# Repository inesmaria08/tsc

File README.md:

# InkTime Smartwatch v5 - Documentație Hardware (DVT)

Acest repository conține pachetul complet de proiectare hardware (schematică, layout PCB, fișiere de fabricație) pentru **InkTime**, un smartwatch ultra-low-power. Proiectul este axat pe eficientizarea consumului energetic și integrarea unui afișaj bi-stabil, eliminând limitările de autonomie specifice dispozitivelor portabile convenționale.

---

## 1. Subsisteme Hardware Integrate

Arhitectura sistemului a fost segmentată în blocuri funcționale clare, utilizând componente specializate pentru a minimiza consumul de energie în modul stand-by (parasitic draw).

### 1.1. Microcontroller și RF
Implementarea are la bază SoC-ul **Nordic Semiconductor nRF52840**, selectat pentru eficiența superioară în gestionarea stivei Bluetooth 5.0 (BLE). Secțiunea RF integrează o antenă ceramică SMD de 2.45GHz (Johanson 2450AT18). Pentru a menține integritatea semnalului radio și a asigura o propagare optimă, zona de sub antenă a fost tratată ca o zonă strictă de "Keep-out", fiind complet izolată de planurile de cupru pe toate straturile PCB-ului.

### 1.2. Power Management Unit (PMIC)
Pentru a garanta o funcționare stabilă a display-ului e-Paper, sensibil la fluctuațiile de tensiune specifice descărcării acumulatorului Li-Po, arhitectura de alimentare exclude regulatoarele LDO clasice în favoarea unor soluții cu randament ridicat:
* **RT6160A:** Regulator Buck-Boost de înaltă eficiență, capabil să mențină o ieșire stabilă de 3.3V pe întreg parcursul descărcării bateriei (4.2V - 3.0V).
* **BQ25180:** Circuit integrat de încărcare liniară, conectat direct la portul USB-C (16-pin) și protejat împotriva descărcărilor electrostatice (ESD) de cipul USBLC6-2SC6Y.
* **MAX17048:** Fuel Gauge care implementează algoritmul ModelGauge pentru monitorizarea precisă a stării de încărcare a bateriei (State of Charge), eliminând necesitatea unui rezistor de shunt și comunicând via I2C.

### 1.3. Interfață Utilizator și Senzori
* **Display e-Paper:** Conectat prin intermediul magistralei SPI (conector Molex FPC cu 24 de pini). Datorită tehnologiei bi-stabile, consumul de curent pentru reținerea imaginii este nul.
* **IMU (Inertial Measurement Unit):** Accelerometrul triaxial ultra-low-power Bosch BMA423 este utilizat pentru detectarea mișcării și activarea sistemului (tilt-to-wake), comunicând prin I2C și semnale de întrerupere hardware.
* **Feedback Haptic:** Driver-ul DRV2605 (Texas Instruments) controlează motorul de vibrație ERM, gestionând efecte haptice pre-procesate fără a încărca suplimentar procesorul principal.
* **Input Hardware:** Trei butoane tactile SMD conectate direct la porturile GPIO (cu rezistențe pull-up interne) pentru navigarea în meniul dispozitivului.

---

## 2. Considerente de Producție (PCBA) și Reguli DFM

Designul a fost optimizat riguros pentru a îndeplini cerințele fabricării la scară (Design for Manufacturing) și pentru a asigura o integrare mecanică perfectă în carcasa smartwatch-ului:

1. **Optimizare PCBA:** Toate componentele SMD sunt plasate exclusiv pe stratul superior (TOP Layer). Această abordare reduce masiv complexitatea, timpul și costurile procesului automatizat Pick & Place. Placa de bază a fost proiectată pentru o grosime a substratului de 1.0mm, vitală pentru menținerea unui profil subțire (low-profile) al ansamblului final.
2. **Reguli de Rutare și Putere:** Traseele de alimentare (VCC, VBUS, 3V3) au fost rutate cu o lățime sigură de minimum 0.3mm pentru a suporta vârfurile de consum (în special în timpul refresh-ului e-Paper și activării motorului haptic). Magistralele de semnal de mare viteză utilizează o lățime de 0.15mm.
3. **Integritate RF și Planuri de Masă:** S-au implementat planuri de masă continue (GND) atât pe stratul TOP, cât și pe BOTTOM. S-a utilizat tehnica de "via stitching" manual, cu o densitate crescută în proximitatea circuitului radio și a convertorului DC/DC, pentru a oferi o cale de retur de impedanță minimă și a reduce emisiile EMI.

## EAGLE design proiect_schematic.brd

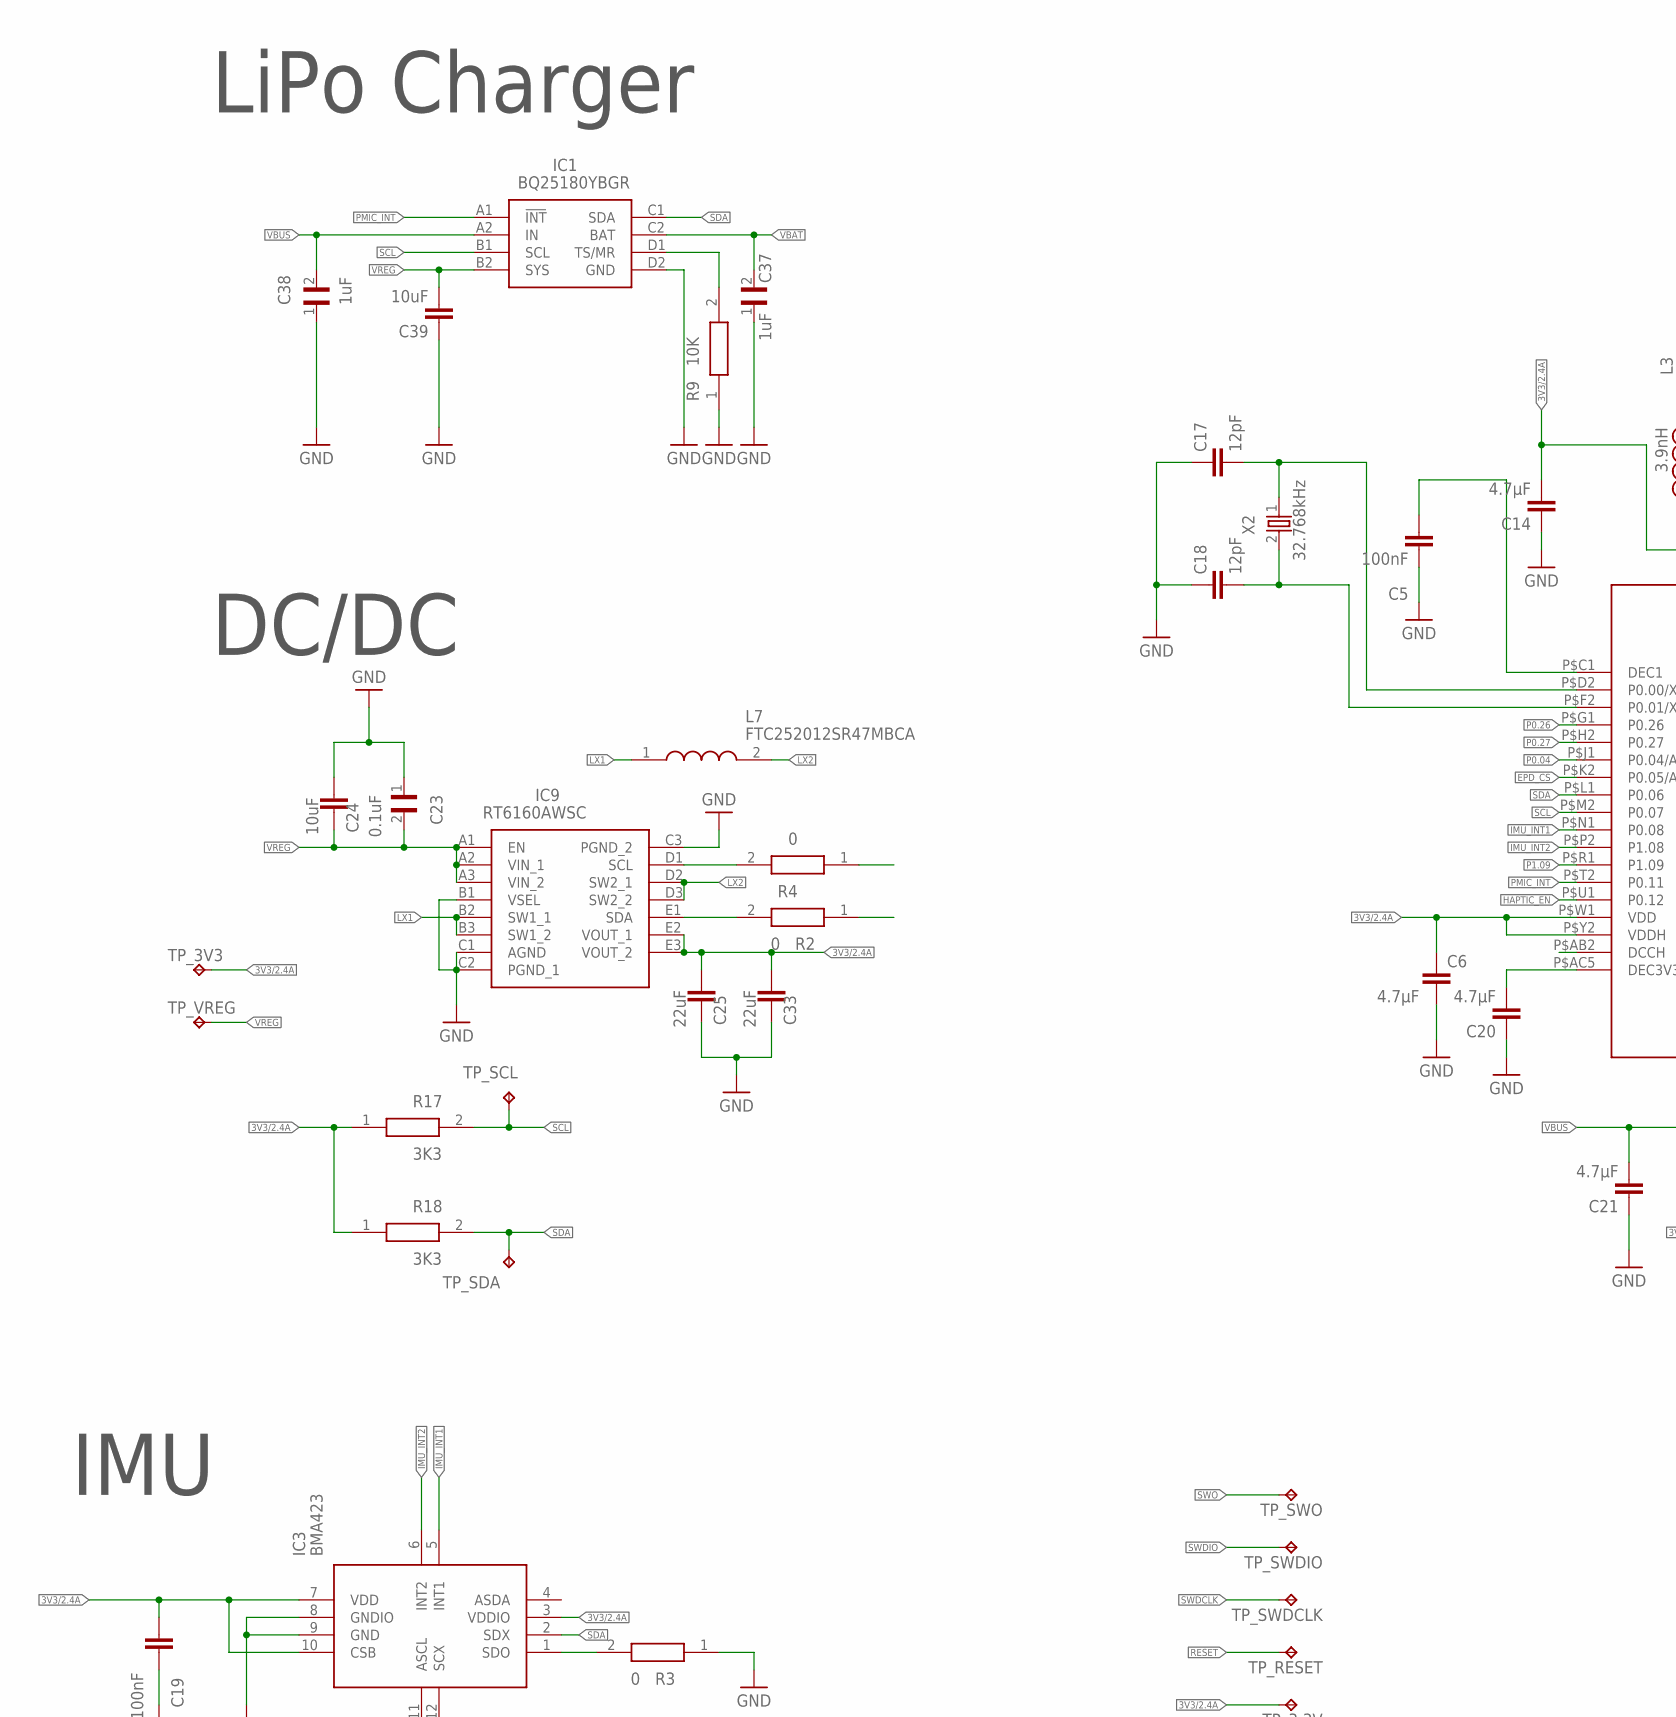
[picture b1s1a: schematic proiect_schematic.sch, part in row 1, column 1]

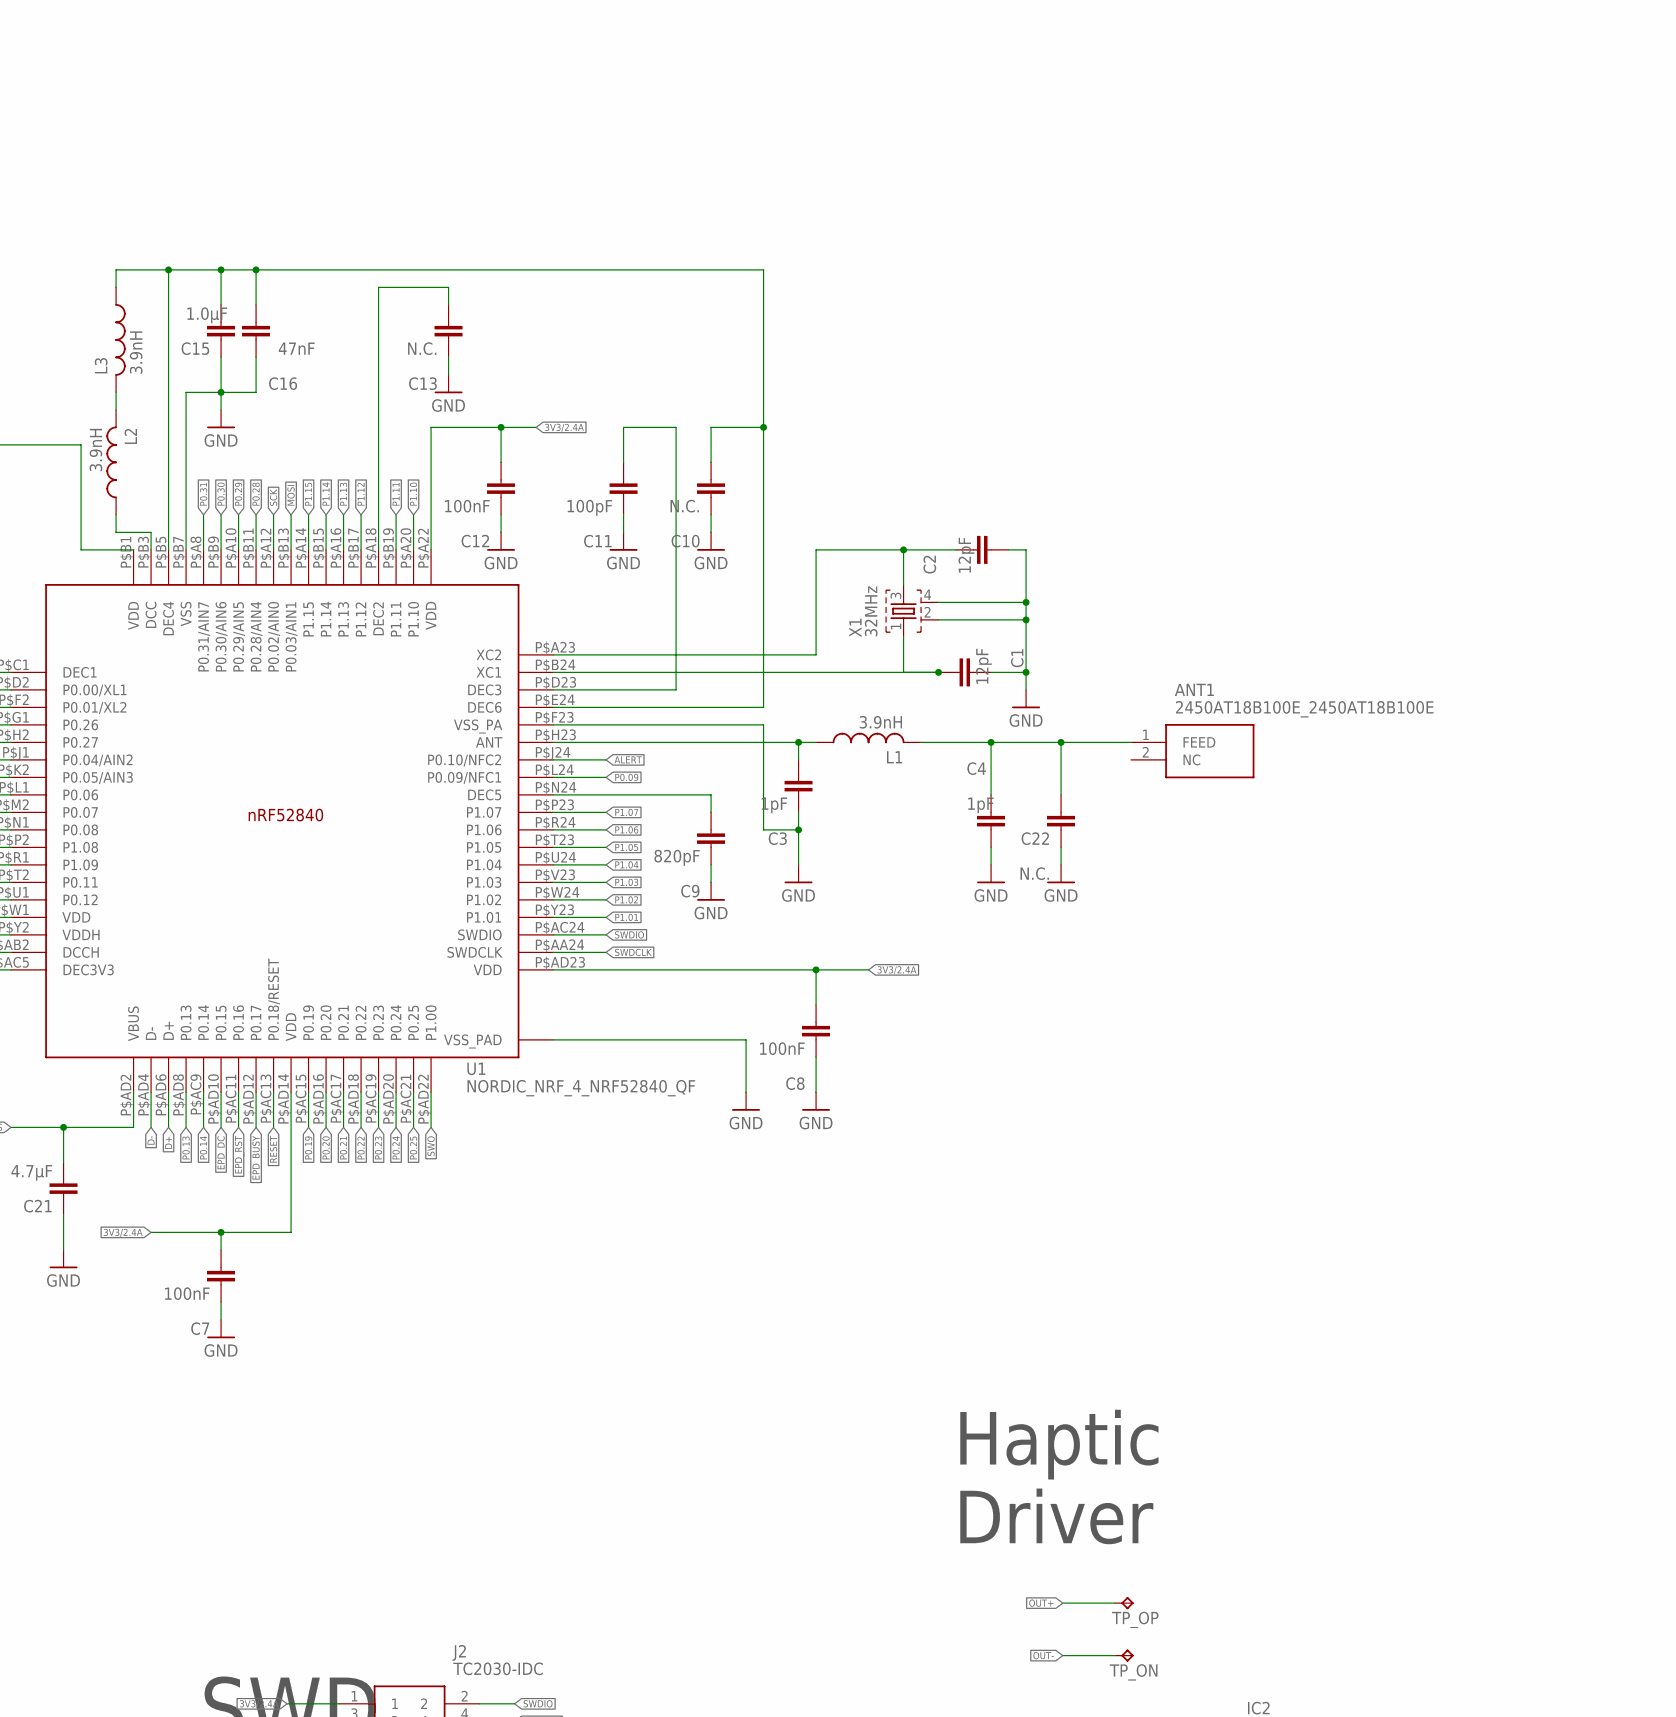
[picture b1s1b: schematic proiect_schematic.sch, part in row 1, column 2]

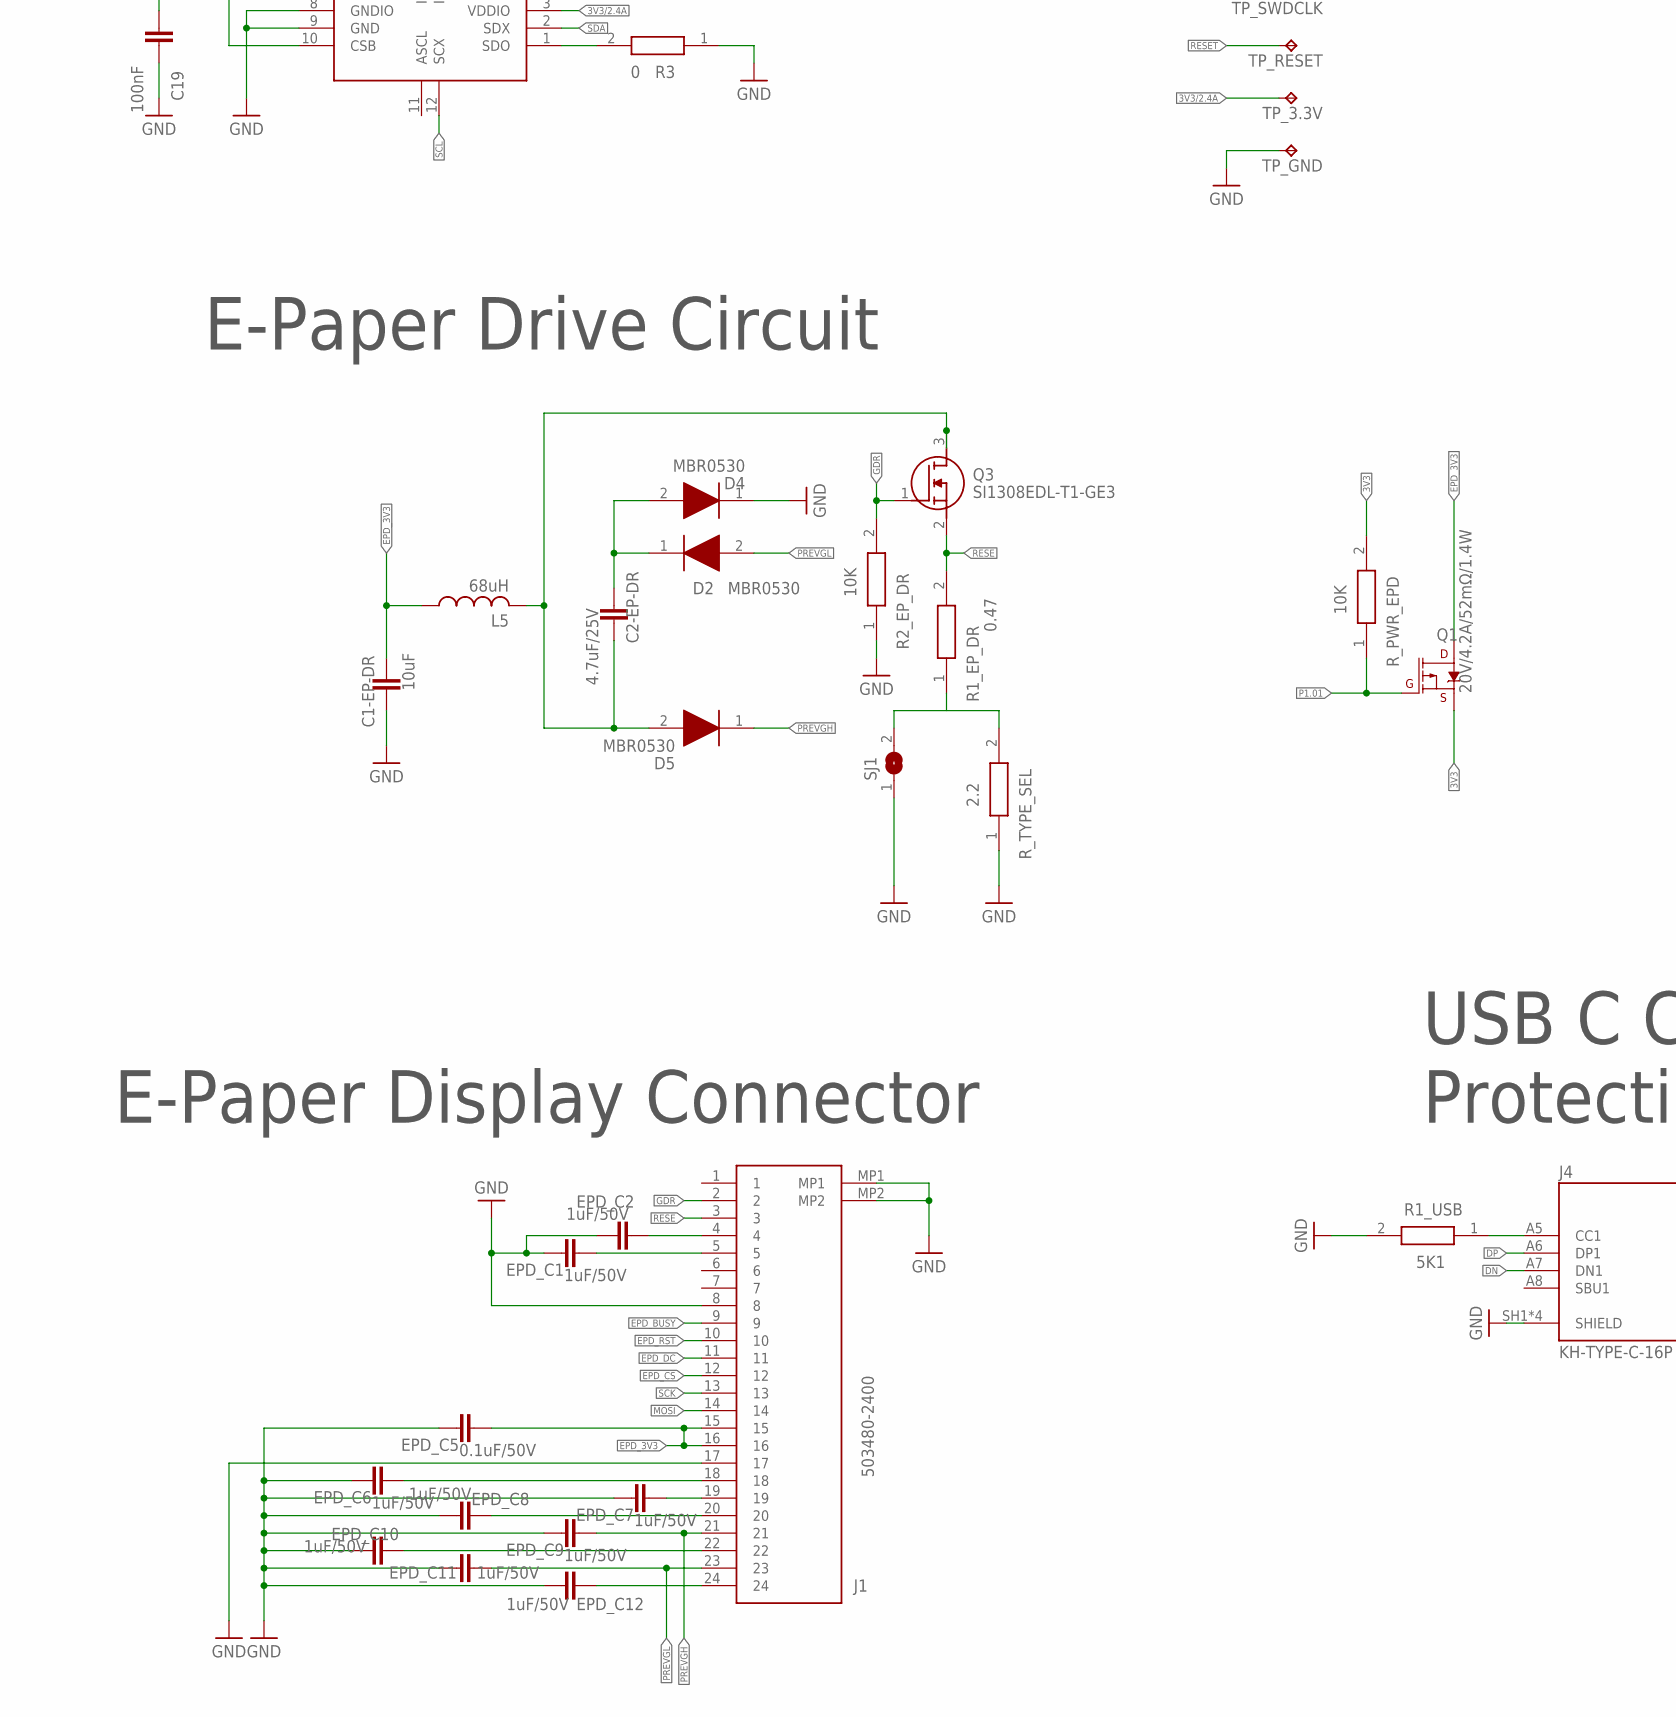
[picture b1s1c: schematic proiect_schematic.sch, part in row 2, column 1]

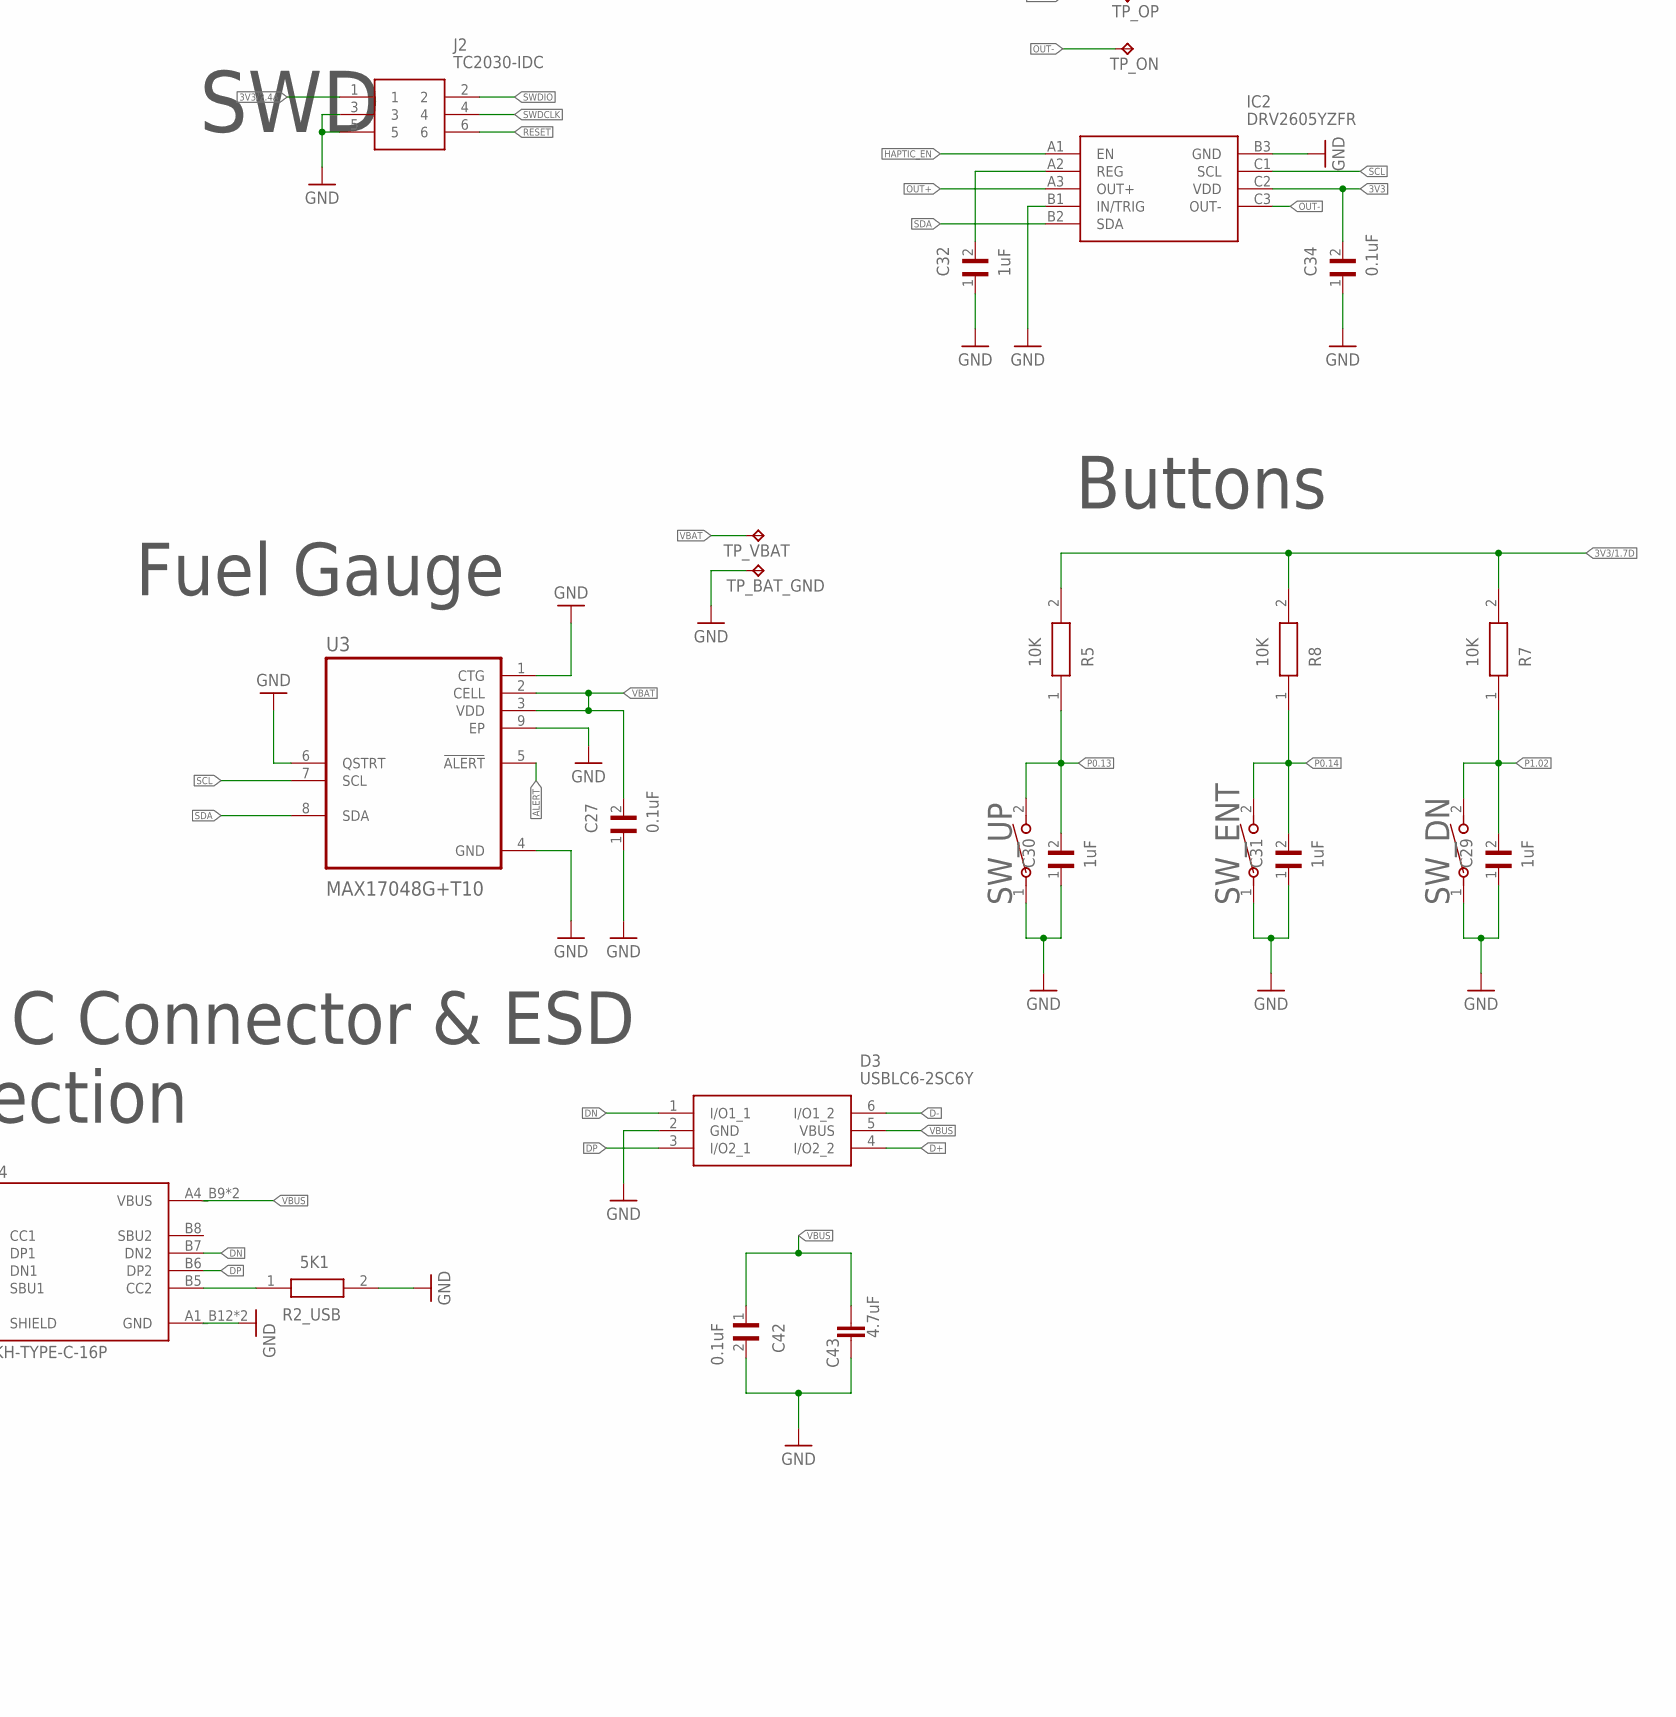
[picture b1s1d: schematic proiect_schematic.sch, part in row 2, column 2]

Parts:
ANT1: 2450AT18B100E_2450AT18B100E; 2450AT18B100E_ANTC3216X140N
C1, C2: 12pF; NORDIC_NRF_3_RESC0201_N
C1-EP-DR, C24, C39: 10uF; PERFECT_0402_0402
C2-EP-DR: 4.7uF/25V; PERFECT_0402_0402
C3, C4: 1pF; NORDIC_NRF_3_RESC0201_N
C5, C7, C8, C12, C19: 100nF; NORDIC_NRF_3_RESC0201_N
C6, C14, C20, C21: 4.7µF; PERFECT_0402_0402
C9: 820pF; NORDIC_NRF_3_RESC0201_N
C10, C13, C22: N.C.; NORDIC_NRF_3_RESC0201_N
C11: 100pF; NORDIC_NRF_3_RESC0201_N
C15: 1.0µF; PERFECT_0402_0402
C16: 47nF; NORDIC_NRF_3_RESC0201_N
C17, C18: 12pF; PERFECT_0402_0402
C23, C27, C34, C42: 0.1uF; GRM011R60J152KE01L_2_CAPC0201X13N
C25, C33: 22uF; PERFECT_0402_0402
C29, C30, C31, C32, C37, C38: 1uF; GRM011R60J152KE01L_2_CAPC0201X13N
C43: 4.7uF; PERFECT_0402_0402
D2, D4, D5: MBR0530; ESP32_C6_LIBRARY_5_SOD3716X135N
D3: USBLC6-2SC6Y; ESP32_C6_LIBRARY_3_SOT95P280X145-6N
EPD_C1, EPD_C2, EPD_C6, EPD_C7, EPD_C8, EPD_C9, EPD_C10, EPD_C11, EPD_C12: 1uF/50V; PERFECT_0402_0402
EPD_C5: 0.1uF/50V; PERFECT_0402_0402
IC1: BQ25180YBGR; BQ25180YBGR_BGA8C40P2X4_100X155X50
IC2: DRV2605YZFR; DRV2605YZFR_BGA9C50P3X3_144X144X62
IC3: BMA423; BMA423_BMA423
IC9: RT6160AWSC; RT6160AWSC_BGA15C40P3X5_140X230X60
J1: 503480-2400; 503480-2400_5034802400
J2: TC2030-IDC; TC2030-IDC_TC2030IDC
J4: KH-TYPE-C-16P; KH-TYPE-C-16P_KINGHELM_KH-TYPE-C-16P
L1, L2, L3: 3.9nH; NORDIC_NRF_2_RESC0402_L
L5: 68uH; NORDIC_NRF_2_RESC0402_L
L7: FTC252012SR47MBCA; MLP2016SR47MT0S1_INDC2016X100N
Q1: 20V/4.2A/52mΩ/1.4W; ESP32_C6_LIBRARY_4_ESP32_C6_LIBRARY_4_ESP32_C6_LIBRARY_4_ES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
Q3: SI1308EDL-T1-GE3; ESP32_C6_LIBRARY_6_SOT65P210X110-3N
R1_EP_DR: 0.47; CPF0201D7K68C1_0201
R1_USB, R2_USB: 5K1; CPF0201D7K68C1_0201
R2, R3, R4: 0; CPF0201D7K68C1_0201
R2_EP_DR, R5, R7, R8, R9: 10K; CPF0201D7K68C1_0201
R17, R18: 3K3; CPF0201D7K68C1_0201
R_PWR_EPD: 10K; CPF0201D7K68C1_0201
R_TYPE_SEL: 2.2; CPF0201D7K68C1_0201
SJ1: ESP32_C6_LIBRARY_7_JUMPER_SJ
SW_DN: 2025-10-22_07-23-44_LIBRARY_EVP-AKE31ASW_EVP-AKE3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; 2025-10-22_07-23-44_LIBRARY_SW_EVP-AKE31A_PAN
SW_ENT: 2025-10-22_07-23-44_LIBRARY_EVP-AKE31ASW_EVP-AKE3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; 2025-10-22_07-23-44_LIBRARY_SW_EVP-AKE31A_PAN
SW_UP: 2025-10-22_07-23-44_LIBRARY_EVP-AKE31ASW_EVP-AKE3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; 2025-10-22_07-23-44_LIBRARY_SW_EVP-AKE31A_PAN
TP_3.3V, TP_3V3: HECTOR_WATCH_1_TPTP20R; HECTOR_WATCH_1_TP20R
TP_BAT_GND: HECTOR_WATCH_1_TPTP20R; HECTOR_WATCH_1_TP20R
TP_GND: HECTOR_WATCH_1_TPTP20R; HECTOR_WATCH_1_TP20R
TP_ON: HECTOR_WATCH_1_TPTP20R; HECTOR_WATCH_1_TP20R
TP_OP: HECTOR_WATCH_1_TPTP20R; HECTOR_WATCH_1_TP20R
TP_RESET: HECTOR_WATCH_1_TPTP20R; HECTOR_WATCH_1_TP20R
TP_SCL: HECTOR_WATCH_1_TPTP20R; HECTOR_WATCH_1_TP20R
TP_SDA: HECTOR_WATCH_1_TPTP20R; HECTOR_WATCH_1_TP20R
TP_SWDCLK: HECTOR_WATCH_1_TPTP20R; HECTOR_WATCH_1_TP20R
TP_SWDIO: HECTOR_WATCH_1_TPTP20R; HECTOR_WATCH_1_TP20R
TP_SWO: HECTOR_WATCH_1_TPTP20R; HECTOR_WATCH_1_TP20R
TP_VBAT: HECTOR_WATCH_1_TPTP20R; HECTOR_WATCH_1_TP20R
TP_VREG: HECTOR_WATCH_1_TPTP20R; HECTOR_WATCH_1_TP20R
U1: NORDIC_NRF_4_NRF52840_QF; NORDIC_NRF_4_AQFN50P700X700X85_HS-74N
U3: MAX17048G+T10; ESP32_C6_LIBRARY_SON50P200X200X80-9N
X1: 32MHz; NORDIC_NRF_BT-XTAL_2016_N
X2: 32.768kHz; NORDIC_NRF_1_XTAL_3215_N

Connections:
3V3: C34.2, IC2.C2 (VDD), Q1.2 (S), R_PWR_EPD.2
3V3/1.7D: R5.2, R7.2, R8.2
3V3/2.4A: C6.1, C7.2, C8.2, C12.2, C14.2, C19.2, C25.2, C33.2, IC3.3 (VDDIO), IC3.7 (VDD), IC3.10 (CSB), IC9.E2 (VOUT_1), IC9.E3 (VOUT_2), J2.1, R17.1, R18.1, TP_3.3V.TP, TP_3V3.TP, U1.P$A22 (VDD), U1.P$AD14 (VDD), U1.P$AD23 (VDD), U1.P$B1 (VDD), U1.P$W1 (VDD), U1.P$Y2 (VDDH)
ALERT: U1.P$J24 (P0.10/NFC2), U3.5 (!ALERT)
D+: D3.4 (I/O2_2), U1.P$AD6 (D+)
D-: D3.6 (I/O1_2), U1.P$AD4 (D-)
DN: D3.1 (I/O1_1), J4.A7 (DN1), J4.B7 (DN2)
DP: D3.3 (I/O2_1), J4.A6 (DP1), J4.B6 (DP2)
EPD_3V3: C1-EP-DR.1, EPD_C5.1, J1.15, J1.16, L5.1, Q1.3 (D)
EPD_BUSY: J1.9, U1.P$AD12 (P0.17)
EPD_CS: J1.12, U1.P$K2 (P0.05/AIN3)
EPD_DC: J1.11, U1.P$AD10 (P0.15)
EPD_RST: J1.10, U1.P$AC11 (P0.16)
GDR: J1.2, Q3.1 (G), R2_EP_DR.2
GND: C1.1, C1-EP-DR.2, C2.2, C3.1, C4.2, C5.1, C6.2, C7.1, C8.1, C9.1, C10.1, C11.1, C12.1, C13.1, C14.1, C15.1, C16.1, C17.1, C18.1, C19.1, C20.1, C21.1, C22.1, C23.1, C24.2, C25.1, C27.1, C29.1, C30.1, C31.1, C32.1, C33.1, C34.1, C37.1, C38.1, C39.1, C42.2, C43.2, D3.2 (GND), D4.1 (K), EPD_C1.2, EPD_C2.1, EPD_C5.2, EPD_C6.2, EPD_C7.2, EPD_C8.1, EPD_C9.2, EPD_C10.1, EPD_C11.2, EPD_C12.1, IC1.D2 (GND), IC2.B1 (IN/TRIG), IC2.B3 (GND), IC3.8 (GNDIO), IC3.9 (GND), IC9.B1 (VSEL), IC9.C1 (AGND), IC9.C2 (PGND_1), IC9.C3 (PGND_2), J1.8, J1.17, J1.MP1, J1.MP2, J2.3, J2.5, J4.A1_B12 (GND), J4.A12_B1 (GND), J4.SH1 (SHIELD), J4.SH2 (SHIELD), J4.SH3 (SHIELD), J4.SH4 (SHIELD), R1_USB.2, R2_EP_DR.1, R2_USB.2, R3.1, R9.1, R_TYPE_SEL.1, SJ1.1, SW_DN.1, SW_ENT.1, SW_UP.1, TP_BAT_GND.TP, TP_GND.TP, U1.P$74 (VSS_PAD), U1.P$75 (VSS_PAD), U1.P$76 (VSS_PAD), U1.P$77 (VSS_PAD), U1.P$78 (VSS_PAD), U1.P$79 (VSS_PAD), U1.P$80 (VSS_PAD), U1.P$81 (VSS_PAD), U1.P$82 (VSS_PAD), U1.P$83 (VSS_PAD), U1.P$84 (VSS_PAD), U1.P$85 (VSS_PAD), U1.P$86 (VSS_PAD), U1.P$87 (VSS_PAD), U1.P$88 (VSS_PAD), U1.P$89 (VSS_PAD), U1.P$90 (VSS_PAD), U1.P$B7 (VSS), U1.P$F23 (VSS_PA), U3.1 (CTG), U3.4 (GND), U3.6 (QSTRT), U3.9 (EP), X1.2, X1.4
HAPTIC_EN: IC2.A1 (EN), U1.P$U1 (P0.12)
IMU_INT1: IC3.5 (INT1), U1.P$N1 (P0.08)
IMU_INT2: IC3.6 (INT2), U1.P$P2 (P1.08)
LX1: IC9.B2 (SW1_1), IC9.B3 (SW1_2), L7.1
LX2: IC9.D2 (SW2_1), IC9.D3 (SW2_2), L7.2
MOSI: J1.14, U1.P$B13 (P0.03/AIN1)
unnamed: C5.2, U1.P$C1 (DEC1)
unnamed: C17.2, U1.P$D2 (P0.00/XL1), X2.1
unnamed: C18.2, U1.P$F2 (P0.01/XL2), X2.2
unnamed: C9.2, U1.P$N24 (DEC5)
unnamed: ANT1.1 (FEED), C4.1, C22.2, L1.2
unnamed: C3.2, L1.1, U1.P$H23 (ANT)
unnamed: C10.2, C15.2, C16.2, L3.1, U1.P$B5 (DEC4), U1.P$E24 (DEC6)
unnamed: C11.2, U1.P$D23 (DEC3)
unnamed: C1.2, U1.P$B24 (XC1), X1.1
unnamed: C2.1, U1.P$A23 (XC2), X1.3
unnamed: L2.2, L3.2
unnamed: L2.1, U1.P$B3 (DCC)
unnamed: IC9.D1 (SCL), R4.2
unnamed: IC9.E1 (SDA), R2.2
unnamed: C20.2, U1.P$AC5 (DEC3V3)
unnamed: J4.A5 (CC1), R1_USB.1
unnamed: C2-EP-DR.1, D5.2 (A), L5.2, Q3.3 (D)
unnamed: IC1.D1 (TS/MR), R9.2
unnamed: C2-EP-DR.2, D2.1 (K), D4.2 (A)
unnamed: EPD_C6.1, J1.18
unnamed: EPD_C2.2, J1.4
unnamed: R_TYPE_SEL.2, SJ1.2
unnamed: IC3.1 (SDO), R3.2
unnamed: EPD_C7.1, J1.19
unnamed: EPD_C1.1, J1.5
unnamed: EPD_C8.2, J1.20
unnamed: C13.2, U1.P$A18 (DEC2)
unnamed: EPD_C10.2, J1.22
unnamed: EPD_C12.2, J1.24
unnamed: C32.2, IC2.A2 (REG)
unnamed: J4.B5 (CC2), R2_USB.1
OUT+: IC2.A3 (OUT+), TP_OP.TP
OUT-: IC2.C3 (OUT-), TP_ON.TP
P0.04: U1.P$J1 (P0.04/AIN2)
P0.09: U1.P$L24 (P0.09/NFC1)
P0.13: C30.2, R5.1, SW_UP.2, U1.P$AD8 (P0.13)
P0.14: C31.2, R8.1, SW_ENT.2, U1.P$AC9 (P0.14)
P0.19: U1.P$AC15 (P0.19)
P0.20: U1.P$AD16 (P0.20)
P0.21: U1.P$AC17 (P0.21)
P0.22: U1.P$AD18 (P0.22)
P0.23: U1.P$AC19 (P0.23)
P0.24: U1.P$AD20 (P0.24)
P0.25: U1.P$AC21 (P0.25)
P0.26: U1.P$G1 (P0.26)
P0.27: U1.P$H2 (P0.27)
P0.28: U1.P$B11 (P0.28/AIN4)
P0.29: U1.P$A10 (P0.29/AIN5)
P0.30: U1.P$B9 (P0.30/AIN6)
P0.31: U1.P$A8 (P0.31/AIN7)
P1.01: Q1.1 (G), R_PWR_EPD.1, U1.P$Y23 (P1.01)
P1.02: C29.2, R7.1, SW_DN.2, U1.P$W24 (P1.02)
P1.03: U1.P$V23 (P1.03)
P1.04: U1.P$U24 (P1.04)
P1.05: U1.P$T23 (P1.05)
P1.06: U1.P$R24 (P1.06)
P1.07: U1.P$P23 (P1.07)
P1.09: U1.P$R1 (P1.09)
P1.10: U1.P$A20 (P1.10)
P1.11: U1.P$B19 (P1.11)
P1.12: U1.P$B17 (P1.12)
P1.13: U1.P$A16 (P1.13)
P1.14: U1.P$B15 (P1.14)
P1.15: U1.P$A14 (P1.15)
PMIC_INT: IC1.A1 (!INT), U1.P$T2 (P0.11)
PREVGH: D5.1 (K), EPD_C9.1, J1.21
PREVGL: D2.2 (A), EPD_C11.1, J1.23
RESE: J1.3, Q3.2 (S), R1_EP_DR.2
RESET: J2.6, TP_RESET.TP, U1.P$AC13 (P0.18/RESET)
SCK: J1.13, U1.P$A12 (P0.02/AIN0)
SCL: IC1.B1 (SCL), IC2.C1 (SCL), IC3.12 (SCX), R17.2, TP_SCL.TP, U1.P$M2 (P0.07), U3.7 (SCL)
SDA: IC1.C1 (SDA), IC2.B2 (SDA), IC3.2 (SDX), R18.2, TP_SDA.TP, U1.P$L1 (P0.06), U3.8 (SDA)
SWDCLK: J2.4, TP_SWDCLK.TP, U1.P$AA24 (SWDCLK)
SWDIO: J2.2, TP_SWDIO.TP, U1.P$AC24 (SWDIO)
SWO: TP_SWO.TP, U1.P$AD22 (P1.00)
VBAT: C27.2, C37.2, IC1.C2 (BAT), TP_VBAT.TP, U3.2 (CELL), U3.3 (VDD)
VBUS: C21.2, C38.2, C42.1, C43.1, D3.5 (VBUS), IC1.A2 (IN), J4.A4_B9 (VBUS), J4.A9_B4 (VBUS), U1.P$AD2 (VBUS)
VREG: C23.2, C24.1, C39.2, IC1.B2 (SYS), IC9.A1 (EN), IC9.A2 (VIN_1), IC9.A3 (VIN_2), TP_VREG.TP

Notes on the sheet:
LiPo Charger
DC/DC
SWD
IMU
Fuel Gauge
E-Paper Drive Circuit
E-Paper Display Connector
USB C Connector & ESD Protection
Haptic Driver
Buttons

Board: 2 copper layers, 105 parts (0 on the bottom side), 72 nets, no tracks yet.

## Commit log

2026-04-10 primul commit
2026-04-21 ultimul commit
2026-04-22 adaugare modele

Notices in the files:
parts and their libraries:
COPYRIGHT: Copyright (C) 2025 Ultra Librarian. All rights reserved.
